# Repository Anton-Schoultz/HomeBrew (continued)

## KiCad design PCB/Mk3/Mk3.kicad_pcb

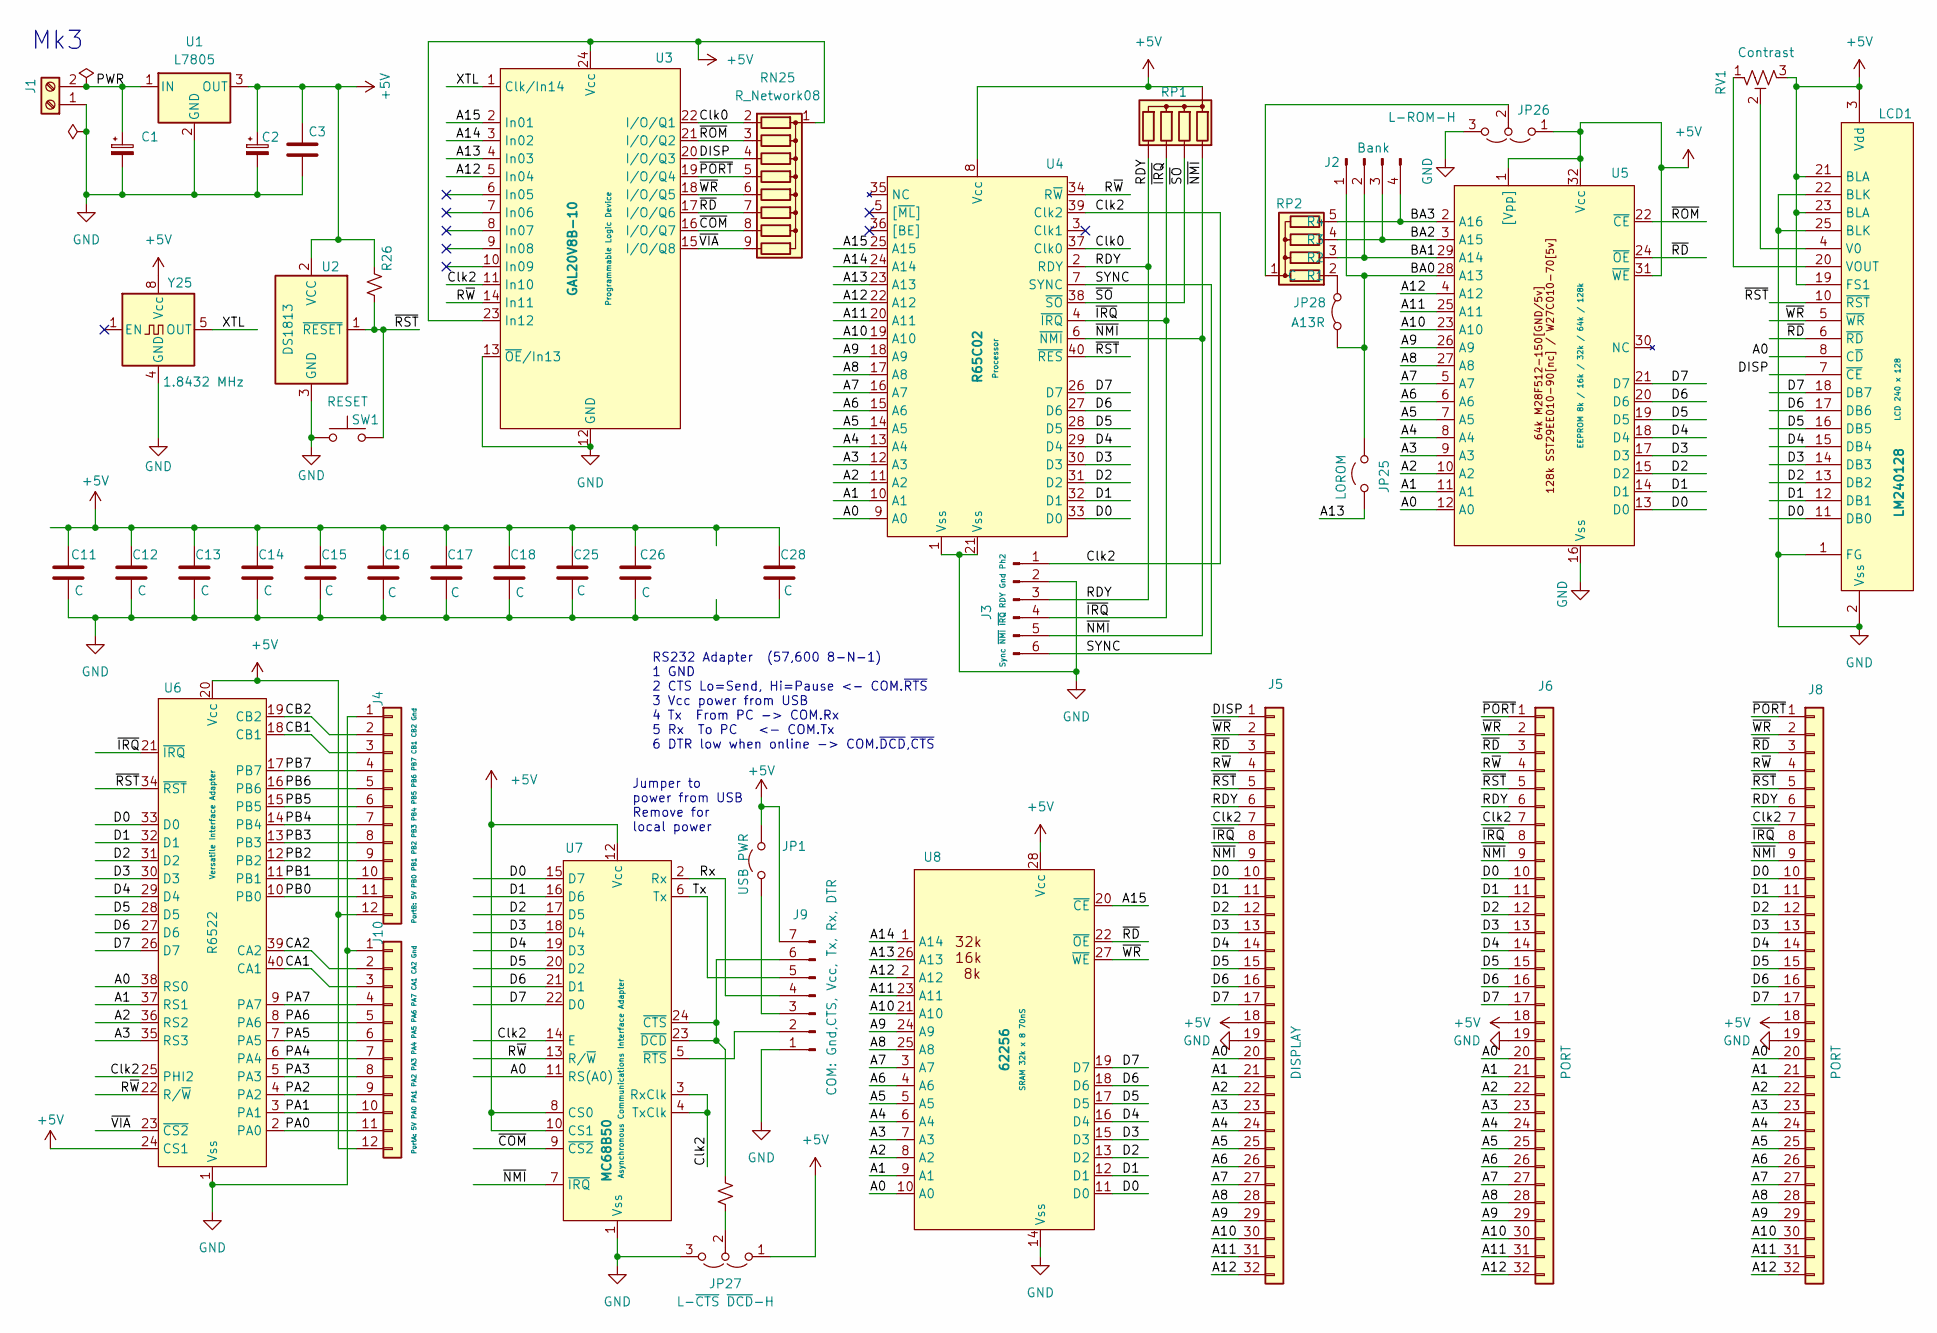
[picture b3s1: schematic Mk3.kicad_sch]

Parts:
C1, C2: C_Polarized_Small; CP_Radial_D10.0mm_P7.50mm
C3, C11, C12, C13, C14, C15, C16, C17, C18, C25, C26, C28: C; C_Disc_D7.5mm_W2.5mm_P5.00mm
J1: Power; TerminalBlock_MaiXu_MX126-5.0-02P_1x02_P5.00mm
J2: Bank; PinHeader_1x04_P2.54mm_Vertical
J3: Sync ~{NMI} ~{IRQ} RDY Gnd Ph2; PinHeader_1x06_P2.54mm_Vertical
J4: PortB: 5V PB0 PB1 PB2 PB3 PB4 PB5 PB6 PB7 CB1 CB2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; PinSocket_1x12_P2.54mm_Vertical
J5: DISPLAY; PinSocket_1x32_P2.54mm_Vertical
J6, J8: PORT; PinSocket_1x32_P2.54mm_Vertical
J9: COM: Gnd,CTS, Vcc, Tx, Rx, DTR; PinSocket_1x07_P2.54mm_Horizontal
J10: PortA: 5V PA0 PA1 PA2 PA3 PA4 PA5 PA6 PA7 CA1 CA2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; PinSocket_1x12_P2.54mm_Vertical
JP1: USB PWR; PinHeader_1x02_P2.54mm_Vertical
JP25: LOROM; PinHeader_1x02_P2.54mm_Vertical
JP26: L-ROM-H; PinHeader_1x03_P2.54mm_Vertical
JP27: L-~{CTS} ~{DCD}-H; PinHeader_1x03_P2.54mm_Vertical
JP28: A13R; SolderJumper-2_P1.3mm_Bridged_RoundedPad1.0x1.5mm
LCD1: LM240128; LCD 240x128
R25: PUp; R_Axial_DIN0204_L3.6mm_D1.6mm_P7.62mm_Horizontal
R26: R_Small_US; R_Axial_DIN0204_L3.6mm_D1.6mm_P7.62mm_Horizontal
RN25: R_Network08; R_Array_SIP9
RP1, RP2: R_Array_SIP5
RV1: Contrast; Potentiometer_Piher_PT-15-V15_Vertical
SW1: RESET; SW_PUSH_1P1T_6x3.5mm_H4.3_APEM_MJTP1243
U1: L7805; TO-220-3_Vertical
U2: DS1813; TO-92L_Wide
U3: GAL20V8B-10; DIP-24_W7.62mm_LongPads
U4: R65C02; DIP-40_W15.24mm_LongPads
U5: EEPROM; DIP-32_W15.24mm_LongPads
U6: R6522; DIP-40_W15.24mm_LongPads
U7: MC68B50; DIP-24_W15.24mm_LongPads
U8: 62256; DIP-28_W15.24mm_LongPads
Y25: 1.8432 MHz; Oscillator_DIP-8

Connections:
+5V: C2.1, C3.1, C11.1, C12.1, C13.1, C14.1, C15.1, C16.1, C17.1, C18.1, C25.1, C26.1, C28.1, J4.12, J5.18, J6.18, J8.18, J9.7, J10.12, JP1.2 (B), JP26.1 (A), JP27.1 (A), LCD1.3 (Vdd), LCD1.19 (FS1), LCD1.21 (BLA), LCD1.23 (BLA), R26.1, RN25.1 (common), RP1.1 (C), RV1.3, U1.3 (OUT), U2.2 (VCC), U3.23 (In12), U3.24 (Vcc), U4.8 (Vcc), U5.1 ([Vpp]), U5.31 (~WE), U5.32 (Vcc), U6.20 (Vcc), U6.24 (CS1), U7.8 (CS0), U7.10 (CS1), U7.12 (Vcc), U8.28 (Vcc), Y25.8 (Vcc)
/A0: J5.20, J6.20, J8.20, LCD1.8 (C~D), U4.9 (A0), U5.12 (A0), U6.38 (RS0), U7.11 (RS(A0)), U8.10 (A0)
/A1: J5.21, J6.21, J8.21, U4.10 (A1), U5.11 (A1), U6.37 (RS1), U8.9 (A1)
/A2: J5.22, J6.22, J8.22, U4.11 (A2), U5.10 (A2), U6.36 (RS2), U8.8 (A2)
/A3: J5.23, J6.23, J8.23, U4.12 (A3), U5.9 (A3), U6.35 (RS3), U8.7 (A3)
/A4: J5.24, J6.24, J8.24, U4.13 (A4), U5.8 (A4), U8.6 (A4)
/A5: J5.25, J6.25, J8.25, U4.14 (A5), U5.7 (A5), U8.5 (A5)
/A6: J5.26, J6.26, J8.26, U4.15 (A6), U5.6 (A6), U8.4 (A6)
/A7: J5.27, J6.27, J8.27, U4.16 (A7), U5.5 (A7), U8.3 (A7)
/A8: J5.28, J6.28, J8.28, U4.17 (A8), U5.27 (A8), U8.25 (A8)
/A9: J5.29, J6.29, J8.29, U4.18 (A9), U5.26 (A9), U8.24 (A9)
/A10: J5.30, J6.30, J8.30, U4.19 (A10), U5.23 (A10), U8.21 (A10)
/A11: J5.31, J6.31, J8.31, U4.20 (A11), U5.25 (A11), U8.23 (A11)
/A12: J5.32, J6.32, J8.32, U3.5 (In04), U4.22 (A12), U5.4 (A12), U8.2 (A12)
/A13: JP25.1 (A), U3.4 (In03), U4.23 (A13), U8.26 (A13)
/A14: U3.3 (In02), U4.24 (A14), U8.1 (A14)
/A15: U3.2 (In01), U4.25 (A15), U8.20 (~CE)
/BA0: J2.1, JP25.2 (B), JP28.1 (A), U5.28 (A13)
/BA1: J2.2, RP2.3 (R2), U5.29 (A14)
/BA2: J2.3, RP2.4 (R3), U5.3 (A15)
/BA3: J2.4, RP2.5 (R4), U5.2 (A16)
/CA1: J10.3, U6.40 (CA1)
/CA2: J10.2, U6.39 (CA2)
/CB1: J4.3, U6.18 (CB1)
/CB2: J4.2, U6.19 (CB2)
/Clk0: RN25.2 (R1), U3.22 (I/O/Q1), U4.37 (Clk0)
/Clk2: J3.1, J5.7, J6.7, J8.7, U3.11 (In10), U4.39 (Clk2), U6.25 (PHI2), U7.3 (RxClk), U7.4 (TxClk), U7.14 (E)
/D0: J5.10, J6.10, J8.10, LCD1.11 (DB0), U4.33 (D0), U5.13 (D0), U6.33 (D0), U7.15 (D7), U8.11 (D0)
/D1: J5.11, J6.11, J8.11, LCD1.12 (DB1), U4.32 (D1), U5.14 (D1), U6.32 (D1), U7.16 (D6), U8.12 (D1)
/D2: J5.12, J6.12, J8.12, LCD1.13 (DB2), U4.31 (D2), U5.15 (D2), U6.31 (D2), U7.17 (D5), U8.13 (D2)
/D3: J5.13, J6.13, J8.13, LCD1.14 (DB3), U4.30 (D3), U5.17 (D3), U6.30 (D3), U7.18 (D4), U8.15 (D3)
/D4: J5.14, J6.14, J8.14, LCD1.15 (DB4), U4.29 (D4), U5.18 (D4), U6.29 (D4), U7.19 (D3), U8.16 (D4)
/D5: J5.15, J6.15, J8.15, LCD1.16 (DB5), U4.28 (D5), U5.19 (D5), U6.28 (D5), U7.20 (D2), U8.17 (D5)
/D6: J5.16, J6.16, J8.16, LCD1.17 (DB6), U4.27 (D6), U5.20 (D6), U6.27 (D6), U7.21 (D1), U8.18 (D6)
/D7: J5.17, J6.17, J8.17, LCD1.18 (DB7), U4.26 (D7), U5.21 (D7), U6.26 (D7), U7.22 (D0), U8.19 (D7)
/DISP: J5.1, LCD1.7 (~CE), RN25.4 (R3), U3.20 (I/O/Q3)
/PA0: J10.11, U6.2 (PA0)
/PA1: J10.10, U6.3 (PA1)
/PA2: J10.9, U6.4 (PA2)
/PA3: J10.8, U6.5 (PA3)
/PA4: J10.7, U6.6 (PA4)
/PA5: J10.6, U6.7 (PA5)
/PA6: J10.5, U6.8 (PA6)
/PA7: J10.4, U6.9 (PA7)
/PB0: J4.11, U6.10 (PB0)
/PB1: J4.10, U6.11 (PB1)
/PB2: J4.9, U6.12 (PB2)
/PB3: J4.8, U6.13 (PB3)
/PB4: J4.7, U6.14 (PB4)
/PB5: J4.6, U6.15 (PB5)
/PB6: J4.5, U6.16 (PB6)
/PB7: J4.4, U6.17 (PB7)
/PWR: C1.1, J1.2, U1.1 (IN)
/RDY: J3.3, J5.6, J6.6, J8.6, RP1.5 (R4), U4.2 (RDY)
/Rx: J9.4, U7.2 (Rx)
/R~W: J5.4, J6.4, J8.4, U3.14 (In11), U4.34 (R~W), U6.22 (R/~W), U7.13 (R/~W)
/SYNC: J3.6, U4.7 (SYNC)
/Tx: J9.5, U7.6 (Tx)
/XTL: U3.1 (Clk/In14), Y25.5 (OUT)
/~COM: RN25.8 (R7), U3.16 (I/O/Q7), U7.9 (~CS2)
/~IRQ: J3.4, J5.8, J6.8, J8.8, RP1.4 (R3), U4.4 (~IRQ), U6.21 (~IRQ)
/~NMI: J3.5, J5.9, J6.9, J8.9, RP1.2 (R1), U4.6 (~NMI), U7.7 (~IRQ)
/~PORT: J6.1, J8.1, RN25.5 (R4), U3.19 (I/O/Q4)
/~RD: J5.3, J6.3, J8.3, LCD1.6 (~RD), RN25.7 (R6), U3.17 (I/O/Q6), U5.24 (~OE), U8.22 (~OE)
/~ROM: RN25.3 (R2), U3.21 (I/O/Q2), U5.22 (~CE)
/~RST: J5.5, J6.5, J8.5, LCD1.10 (~RST), R26.2, SW1.2, U2.1 (~RESET), U4.40 (~RES), U6.34 (~RST)
/~SO: RP1.3 (R2), U4.38 (~SO)
/~VIA: RN25.9 (R8), U3.15 (I/O/Q8), U6.23 (~CS2)
/~WR: J5.2, J6.2, J8.2, LCD1.5 (~WR), RN25.6 (R5), U3.18 (I/O/Q5), U8.27 (~WE)
GND: C1.2, C2.2, C3.2, C11.2, C12.2, C13.2, C14.2, C15.2, C16.2, C17.2, C18.2, C25.2, C26.2, C28.2, J1.1, J3.2, J4.1, J5.19, J6.19, J8.19, J9.1, J10.1, JP26.3 (B), JP27.3 (B), LCD1.1 (FG), LCD1.2 (Vss), LCD1.22 (BLK), LCD1.25 (BLK), SW1.1, U1.2 (GND), U2.3 (GND), U3.12 (GND), U3.13 (~OE/In13), U4.1 (Vss), U4.21 (Vss), U5.16 (Vss), U6.1 (Vss), U7.1 (Vss), U8.14 (Vss), Y25.4 (GND)
unnamed: J9.2, U7.5 (~RTS)
unnamed: J9.3, JP1.1 (A)
unnamed: J9.6, R25.2, U7.23 (~DCD), U7.24 (~CTS)
unnamed: JP26.2 (C), RP2.1 (C)
unnamed: JP27.2 (C), R25.1
unnamed: JP28.2 (B), RP2.2 (R1)
unnamed: LCD1.4 (V0), RV1.2
unnamed: LCD1.20 (VOUT), RV1.1

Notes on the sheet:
Mk3
RS232 Adapter (57,600 8-N-1) 1 GND 2 CTS Lo=Send, Hi=Pause <- COM.~{RTS} 3 Vcc power from USB 4 Tx From PC -> COM.Rx 5 Rx To PC <- COM.Tx 6 DTR low when online -> COM.~{DCD},~{CTS}
Jumper to power from USB Remove for local power

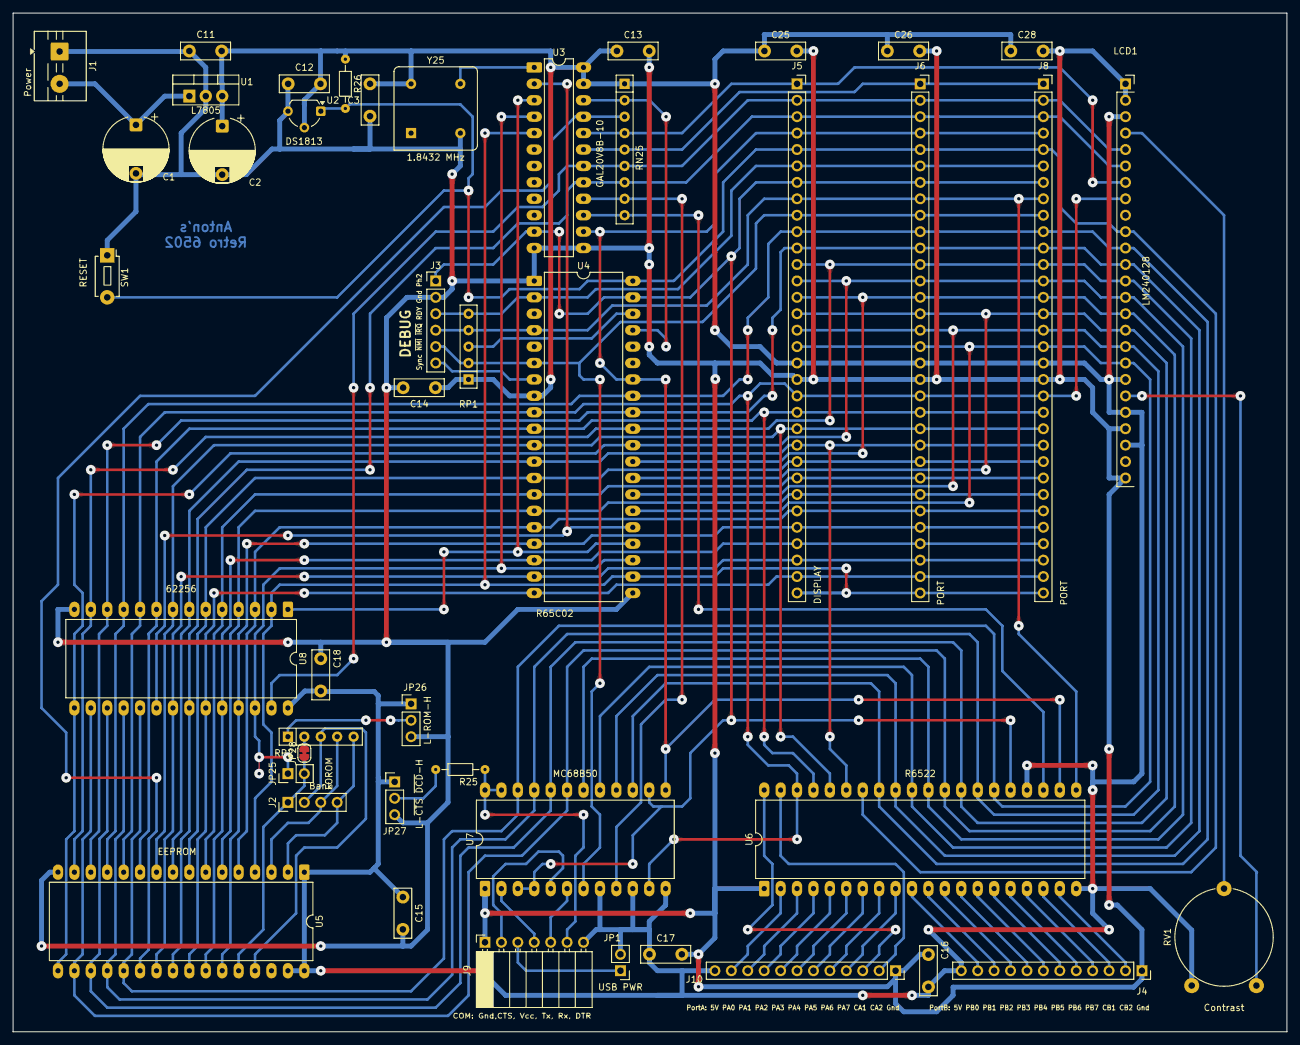
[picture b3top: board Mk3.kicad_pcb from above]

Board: 2 copper layers, 197.0 x 157.5 mm, 45 parts (0 on the bottom side), 78 nets.

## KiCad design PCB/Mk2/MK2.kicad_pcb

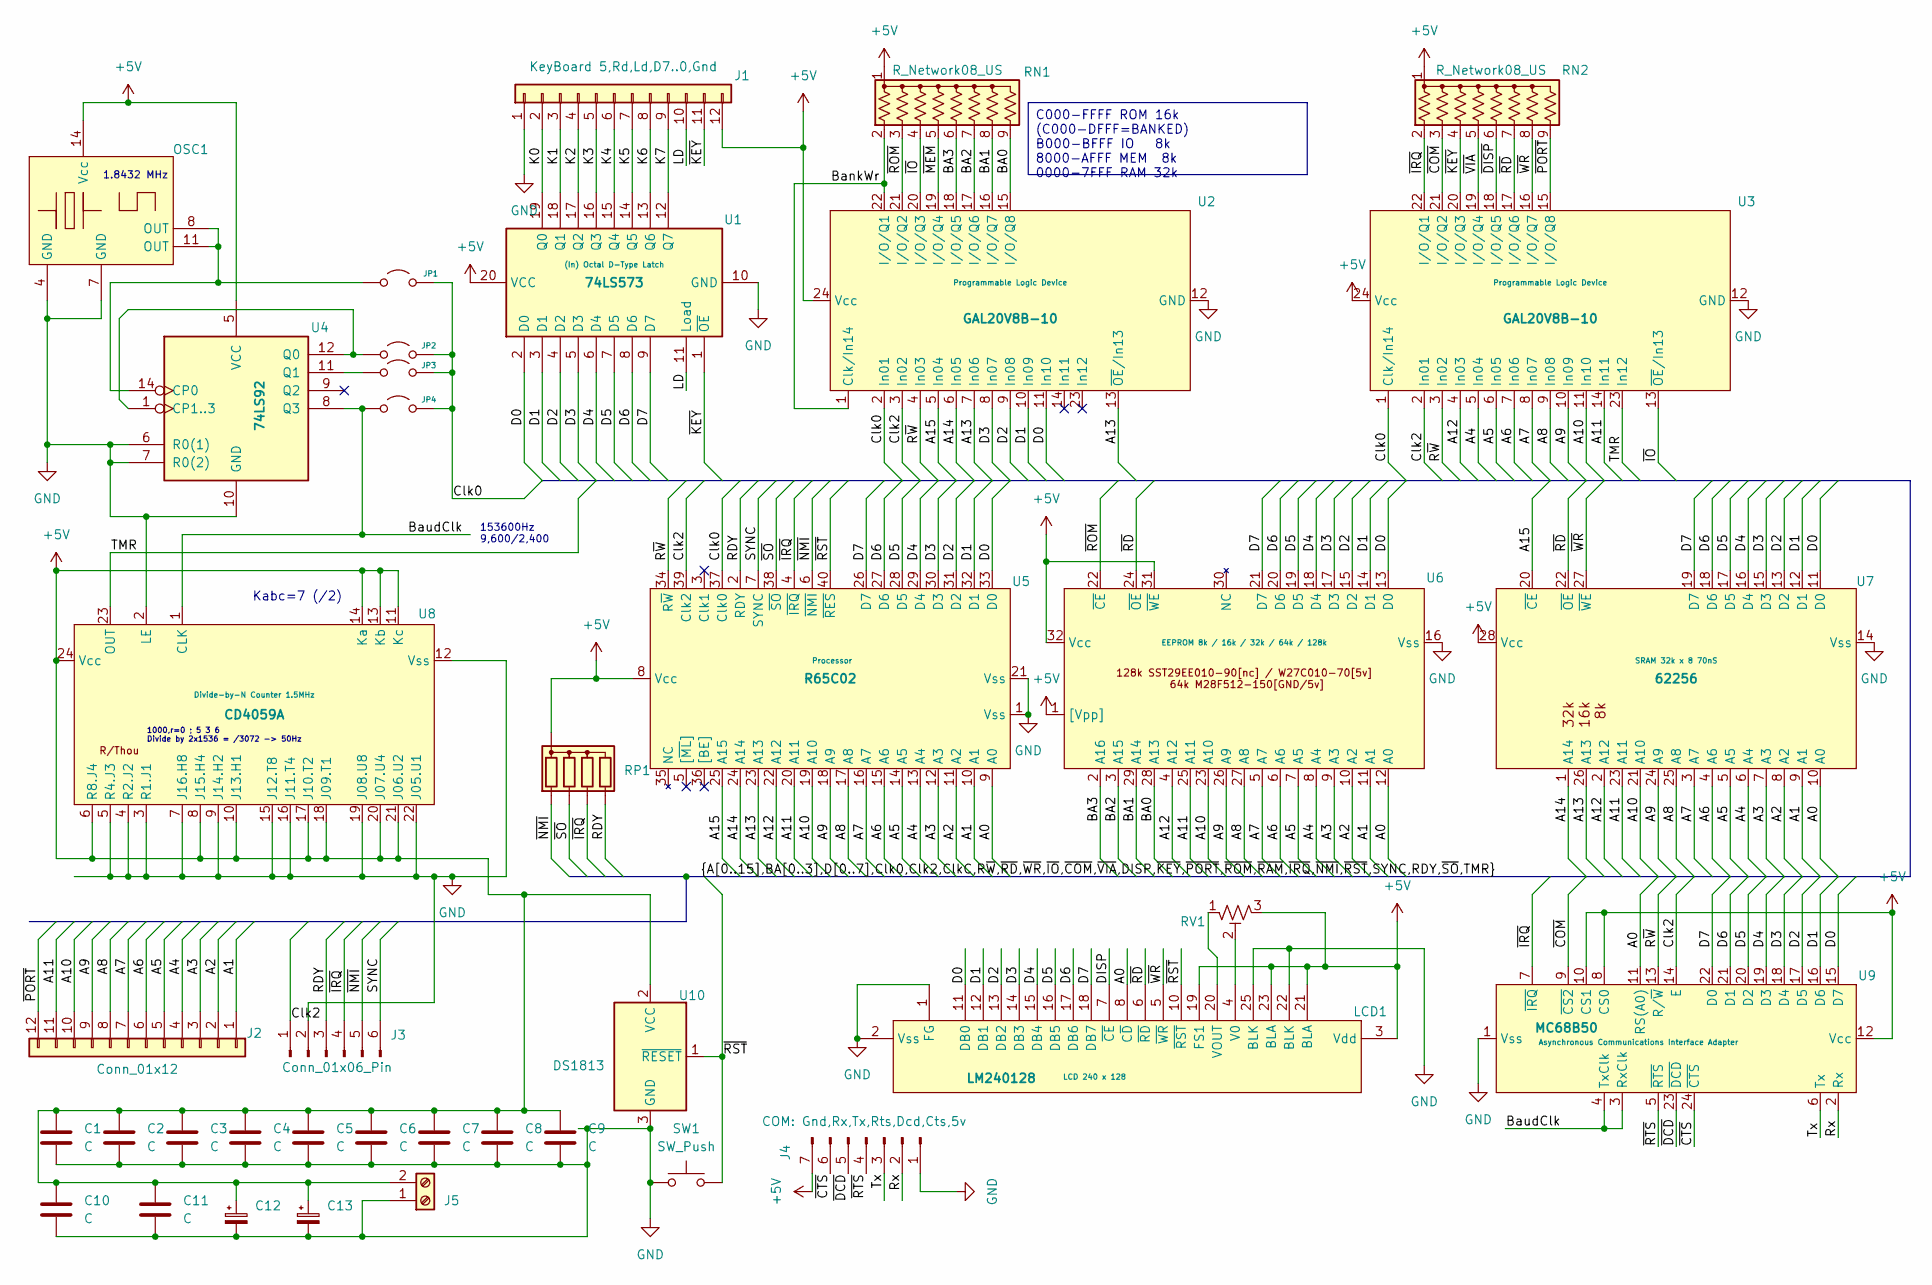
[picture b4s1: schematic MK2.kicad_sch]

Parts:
C1, C3, C4, C6, C7, C8, C9, C10: C; C_Disc_D7.5mm_W2.5mm_P5.00mm
C2, C5, C11: C; C_Rect_L11.0mm_W2.8mm_P10.00mm_MKT
C12, C13: C_Polarized_Small; CP_Radial_D10.0mm_P7.50mm
J1: KeyBoard 5,Rd,Ld,D7..0,Gnd; PinHeader_1x12_P2.54mm_Vertical
J2: Conn_01x12; PinSocket_1x12_P2.54mm_Vertical
J3: Conn_01x06_Pin; PinHeader_1x06_P2.54mm_Vertical
J4: COM: Gnd,Rx,Tx,Rts,Dcd,Cts,5v; PinSocket_1x07_P2.54mm_Horizontal
J5: Screw_Terminal_01x02; TerminalBlock_MaiXu_MX126-5.0-02P_1x02_P5.00mm
JP1, JP2, JP3, JP4: Jumper_2_Open; PinHeader_1x02_P2.54mm_Vertical
LCD1: LM240128; LCD 240x128
OSC1: DIP-14_W7.62mm_LongPads
RN1, RN2: R_Network08_US; R_Array_SIP9
RP1: R_Array_SIP5
RV1: R_Trim; Potentiometer_Runtron_RM-065_Vertical
SW1: SW_Push; MiniSwitch
U1: 74LS573; DIP-20_W7.62mm_LongPads
U2, U3: GAL20V8B-10; DIP-24_W7.62mm_LongPads
U4: 74LS92; DIP-14_W7.62mm
U5: R65C02; DIP-40_W15.24mm_LongPads
U6: EEPROM; DIP-32_W15.24mm_LongPads
U7: 62256; DIP-28_W15.24mm_LongPads
U8: CD4059A; DIP-24_W7.62mm_LongPads
U9: MC68B50; DIP-24_W15.24mm_LongPads
U10: DS1813; TO-92L_Inline

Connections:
+5V: C1.1, C2.1, C3.1, C4.1, C5.1, C6.1, C7.1, C8.1, C9.1, C10.1, C11.1, C12.1, C13.1, J1.12, J4.7, J5.2, LCD1.3 (Vdd), LCD1.19 (FS1), LCD1.21 (BLA), LCD1.23 (BLA), OSC1.14 (Vcc), RN1.1 (common), RN2.1 (common), RP1.1 (C), RV1.3, U1.20 (VCC), U2.24 (Vcc), U3.24 (Vcc), U4.5 (VCC), U5.8 (Vcc), U6.1 ([Vpp]), U6.31 (~WE), U6.32 (Vcc), U7.28 (Vcc), U8.6 (R8.J4), U8.8 (J15.H4), U8.10 (J13.H1), U8.11 (Kc), U8.13 (Kb), U8.14 (Ka), U8.17 (J10.T2), U8.18 (J09.T1), U8.20 (J07.U4), U8.21 (J06.U2), U8.24 (Vcc), U9.8 (CS0), U9.10 (CS1), U9.12 (Vcc), U10.2 (VCC)
/A0: LCD1.8 (C~D), U5.9 (A0), U6.12 (A0), U7.10 (A0), U9.11 (RS(A0))
/A1: J2.1, U5.10 (A1), U6.11 (A1), U7.9 (A1)
/A2: J2.2, U5.11 (A2), U6.10 (A2), U7.8 (A2)
/A3: J2.3, U5.12 (A3), U6.9 (A3), U7.7 (A3)
/A4: J2.4, U3.5 (In04), U5.13 (A4), U6.8 (A4), U7.6 (A4)
/A5: J2.5, U3.6 (In05), U5.14 (A5), U6.7 (A5), U7.5 (A5)
/A6: J2.6, U3.7 (In06), U5.15 (A6), U6.6 (A6), U7.4 (A6)
/A7: J2.7, U3.8 (In07), U5.16 (A7), U6.5 (A7), U7.3 (A7)
/A8: J2.8, U3.9 (In08), U5.17 (A8), U6.27 (A8), U7.25 (A8)
/A9: J2.9, U3.10 (In09), U5.18 (A9), U6.26 (A9), U7.24 (A9)
/A10: J2.10, U3.11 (In10), U5.19 (A10), U6.23 (A10), U7.21 (A10)
/A11: J2.11, U3.14 (In11), U5.20 (A11), U6.25 (A11), U7.23 (A11)
/A12: U3.4 (In03), U5.22 (A12), U6.4 (A12), U7.2 (A12)
/A13: U2.7 (In06), U2.13 (~OE/In13), U5.23 (A13), U7.26 (A13)
/A14: U2.6 (In05), U5.24 (A14), U7.1 (A14)
/A15: U2.5 (In04), U5.25 (A15), U7.20 (~CE)
/BA0: RN1.9 (R8), U2.15 (I/O/Q8), U6.28 (A13)
/BA1: RN1.8 (R7), U2.16 (I/O/Q7), U6.29 (A14)
/BA2: RN1.7 (R6), U2.17 (I/O/Q6), U6.3 (A15)
/BA3: RN1.6 (R5), U2.18 (I/O/Q5), U6.2 (A16)
/BankWr: RN1.2 (R1), U2.1 (Clk/In14), U2.22 (I/O/Q1)
/BaudClk: JP4.1 (A), U4.8 (Q3), U8.1 (CLK), U9.3 (RxClk), U9.4 (TxClk)
/Clk0: JP1.2 (B), JP2.2 (B), JP3.2 (B), JP4.2 (B), U2.2 (In01), U3.1 (Clk/In14), U5.37 (Clk0)
/Clk2: J3.1, U2.3 (In02), U3.2 (In01), U5.39 (Clk2), U9.14 (E)
/D0: LCD1.11 (DB0), U1.2 (D0), U2.11 (In10), U5.33 (D0), U6.13 (D0), U7.11 (D0), U9.15 (D7)
/D1: LCD1.12 (DB1), U1.3 (D1), U2.10 (In09), U5.32 (D1), U6.14 (D1), U7.12 (D1), U9.16 (D6)
/D2: LCD1.13 (DB2), U1.4 (D2), U2.9 (In08), U5.31 (D2), U6.15 (D2), U7.13 (D2), U9.17 (D5)
/D3: LCD1.14 (DB3), U1.5 (D3), U2.8 (In07), U5.30 (D3), U6.17 (D3), U7.15 (D3), U9.18 (D4)
/D4: LCD1.15 (DB4), U1.6 (D4), U5.29 (D4), U6.18 (D4), U7.16 (D4), U9.19 (D3)
/D5: LCD1.16 (DB5), U1.7 (D5), U5.28 (D5), U6.19 (D5), U7.17 (D5), U9.20 (D2)
/D6: LCD1.17 (DB6), U1.8 (D6), U5.27 (D6), U6.20 (D6), U7.18 (D6), U9.21 (D1)
/D7: LCD1.18 (DB7), U1.9 (D7), U5.26 (D7), U6.21 (D7), U7.19 (D7), U9.22 (D0)
/DISP: LCD1.7 (~CE)
/K0: J1.2, U1.19 (Q0)
/K1: J1.3, U1.18 (Q1)
/K2: J1.4, U1.17 (Q2)
/K3: J1.5, U1.16 (Q3)
/K4: J1.6, U1.15 (Q4)
/K5: J1.7, U1.14 (Q5)
/K6: J1.8, U1.13 (Q6)
/K7: J1.9, U1.12 (Q7)
/LD: J1.10, U1.11 (Load)
/RDY: J3.3, RP1.5 (R4), U5.2 (RDY)
/Rx: J4.2, U9.2 (Rx)
/R~W: U2.4 (In03), U3.3 (In02), U5.34 (R~W), U9.13 (R/~W)
/SYNC: J3.6, U5.7 (SYNC)
/TMR: U3.23 (In12), U8.23 (OUT)
/Tx: J4.3, U9.6 (Tx)
/~COM: RN2.3 (R2), U3.21 (I/O/Q2), U9.9 (~CS2)
/~CTS: J4.6, U9.24 (~CTS)
/~DCD: J4.5, U9.23 (~DCD)
/~DISP: RN2.6 (R5), U3.18 (I/O/Q5)
/~IO: RN1.4 (R3), U2.20 (I/O/Q3), U3.13 (~OE/In13)
/~IRQ: J3.4, RN2.2 (R1), RP1.4 (R3), U3.22 (I/O/Q1), U5.4 (~IRQ), U9.7 (~IRQ)
/~KEY: J1.11, RN2.4 (R3), U1.1 (~OE), U3.20 (I/O/Q3)
/~MEM: RN1.5 (R4), U2.19 (I/O/Q4)
/~NMI: J3.5, RP1.2 (R1), U5.6 (~NMI)
/~PORT: J2.12, RN2.9 (R8), U3.15 (I/O/Q8)
/~RD: LCD1.6 (~RD), RN2.7 (R6), U3.17 (I/O/Q6), U6.24 (~OE), U7.22 (~OE)
/~ROM: RN1.3 (R2), U2.21 (I/O/Q2), U6.22 (~CE)
/~RST: LCD1.10 (~RST), SW1.2, U5.40 (~RES), U10.1 (~RESET)
/~RTS: J4.4, U9.5 (~RTS)
/~SO: RP1.3 (R2), U5.38 (~SO)
/~VIA: RN2.5 (R4), U3.19 (I/O/Q4)
/~WR: LCD1.5 (~WR), RN2.8 (R7), U3.16 (I/O/Q7), U7.27 (~WE)
GND: C1.2, C2.2, C3.2, C4.2, C5.2, C6.2, C7.2, C8.2, C9.2, C10.2, C11.2, C12.2, C13.2, J1.1, J3.2, J4.1, J5.1, LCD1.1 (FG), LCD1.2 (Vss), LCD1.22 (BLK), LCD1.25 (BLK), OSC1.4 (GND), OSC1.7 (GND), SW1.1, U1.10 (GND), U2.12 (GND), U3.12 (GND), U4.6 (R0(1)), U4.7 (R0(2)), U4.10 (GND), U5.1 (Vss), U5.21 (Vss), U6.16 (Vss), U7.14 (Vss), U8.2 (LE), U8.3 (R1.J1), U8.4 (R2.J2), U8.5 (R4.J3), U8.7 (J16.H8), U8.9 (J14.H2), U8.12 (Vss), U8.15 (J12.T8), U8.16 (J11.T4), U8.19 (J08.U8), U8.22 (J05.U1), U9.1 (Vss), U10.3 (GND)
unnamed: JP1.1 (A), OSC1.8 (OUT), OSC1.11 (OUT), U4.14 (CP0)
unnamed: JP2.1 (A), U4.1 (CP1..3), U4.12 (Q0)
unnamed: JP3.1 (A), U4.11 (Q1)
unnamed: LCD1.4 (V0), RV1.2
unnamed: LCD1.20 (VOUT), RV1.1

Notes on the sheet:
Kabc=7 (/2)
1.8432 MHz
1000,r=0 ; 5 3 6 Divide by 2x1536 = /3072 -> 50Hz
153600Hz 9,600/2,400
C000-FFFF ROM 16k (C000-DFFF=BANKED) B000-BFFF IO 8k 8000-AFFF MEM 8k 0000-7FFF RAM 32k

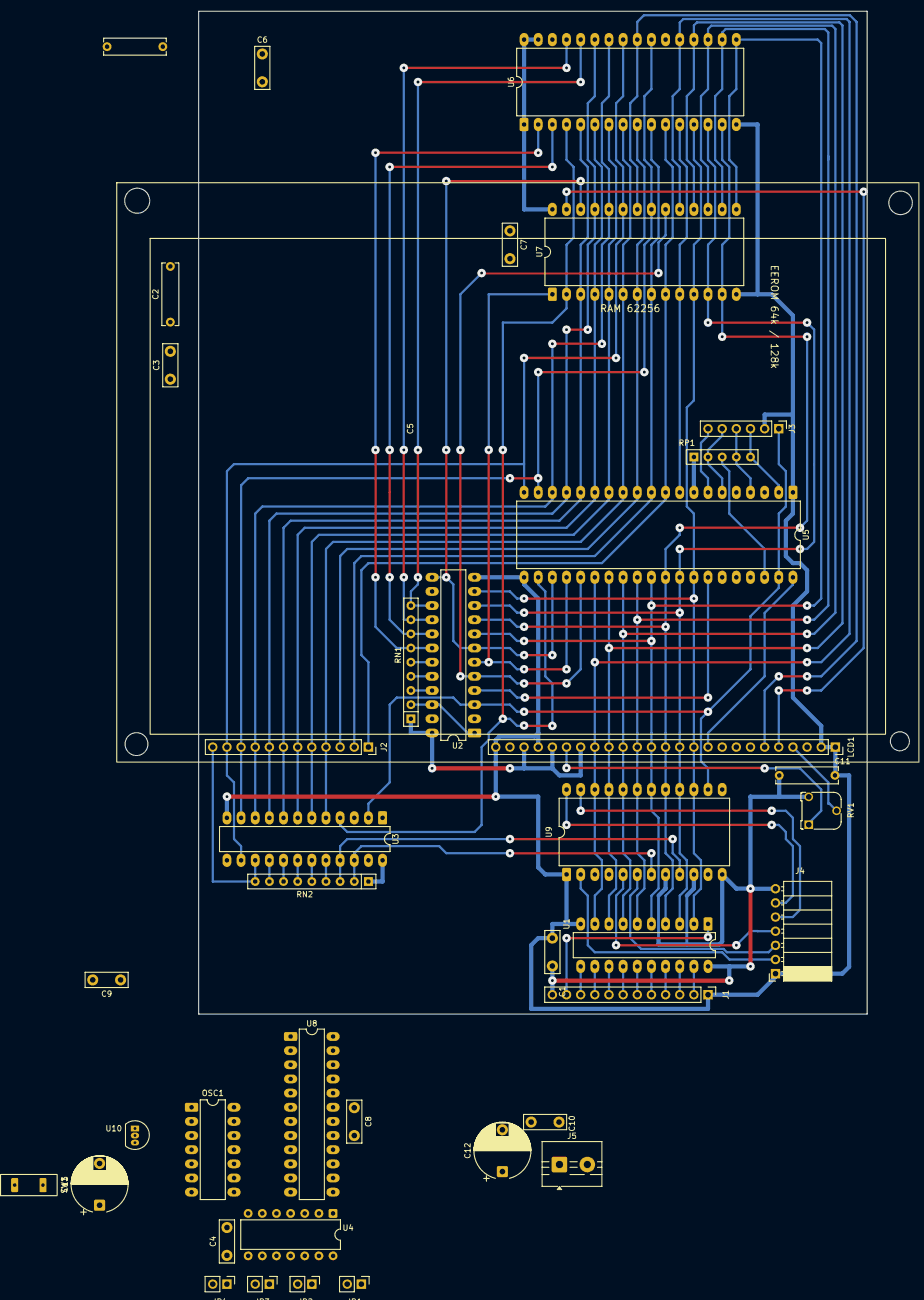
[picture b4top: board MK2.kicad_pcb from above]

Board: 2 copper layers, 141.4 x 180.0 mm, 39 parts (0 on the bottom side), 71 nets.

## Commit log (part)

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2024-11-11 GAL programmer (GAL20v8)
2024-11-11 Added Arduino section
2024-11-11 Added text
2024-11-11 Updated docs
2024-11-11 added pulseview links
2024-11-11 wincupl notes
2024-11-11 added pic of gal hat
2024-11-15 Added EEProgrammer code
2024-11-15 Added EE programmer and updated docs
2024-11-16 Updates to EEProgrammer to count zero bits. Added hex2bin tool
2024-11-19 Removed large install file for kicad-8.0.6-x86_64.exe
    Former-commit-id: 00c60aa45879fdb8a15821be57ce837079a9e464
2024-11-19 Updated read.me files
2024-12-12 Clock Circuit
2024-12-12 updated with pictures
2024-12-12 Fix diagram
2024-12-12 typo
2024-12-12 Datasheets added
2024-12-12 added history
2025-01-14 Renamed
2025-01-30 Additional Data sheets
2025-02-07 update IC labels
2025-02-07 Initial 6502 code bits
2025-02-07 Fix BufBlkWr
2025-02-07 Problem with buffer wrap around
2025-02-10 batch job for UltraEdit to assemble (using uz80as) and convert output
2025-02-12 Start Of Device work
2025-02-18 Modules and S16 Math
2025-02-18 CalcStr and CalcParse
2025-02-19 Save1
2025-02-19 More TestCode added
2025-02-21 Added CharRd, CharWr etc
2025-02-21 save
2025-02-22 Code pretty
2025-02-24 stack check, calc copies
2025-02-25 save point
2025-02-25 Parse & To String
2025-02-25 clean up
2025-02-25 Added rounding to the parse routine
2025-02-26 Adjust multiply result, apply sign and correct EXP for result -> NumA
2025-02-26 Div working, but integer result, need fractional part
2025-02-26 Divide working, problem with CalcStr, CalcStF etc
2025-02-26 Updated batch job, added AsmHelper.jar (asm formatter)
2025-03-03 Start of BASIC code
2025-03-03 Save point for BASIC
2025-03-03 TokFind fix
2025-03-03 Listing initial
2025-03-03 Print of decimal line no working
2025-03-03 NUMBER now 24 Bit
2025-03-03 24 bit macros for add,sub and shift
2025-03-03 24bit comments
2025-03-03 refactor
2025-03-04 Parse/List working?
2025-03-04 ReFormatted
2025-03-04 Updated Formatter (opcode to lowerCase)
2025-03-05 Fixes to Parsing routine
2025-03-06 Added IrqNmi.a65
2025-03-06 Parsing Tokens, Quoted-string, numeric, Var Names - the rest as-is.
2025-03-06 Added Zero blank / suppress
2025-03-06 Added list of Long VarName
2025-03-06 Changes to BREAK(n) handling, use with 'animate' Initial implementation of PRINT Indented echo info to make Assembler Messages stand out more
2025-03-06 Fix Print Number
2025-03-06 Change IntelHEX gen to map to $1000
2025-03-07 Added String and start of Eval
2025-03-07 DBuged StrClr, StrAdd, StrHead, StrTail, StrOut
2025-03-07 Added StrTrim
2025-03-07 Added & DBugged StrUpper, StrLower
2025-03-08 Execute of Print fixed :)
2025-03-08 Refactored Variable/Literal token parsing & listing
2025-03-09 Fixed list of var
2025-03-09 Fixes for long names, using bit7 to mark last char of name (or first if only one)
2025-03-10 Added tokenising of <= <> >=
2025-03-10 Refactoring
2025-03-12 Variables - Parse/list
2025-03-12 Keywords for tokenising
2025-03-12 Simple implementation of PRINT
2025-03-16 Add/Subtract OK, started Mul/Div
2025-03-16 Multiply seems OK, added brackets
2025-03-17 Refactor normalising
2025-03-17 Refactor float offset defs
2025-03-17 Div adjustment working
2025-03-17 Snap shot
2025-03-17 46783cy 385free
2025-03-17 357-44732
2025-03-17 tweak NumMul normalise
2025-03-17 tweak
2025-03-17 pre-tweak Div
2025-03-17 changed to 8k ROM
2025-03-18 pre change to sgn & exp as part of the 8 bytes
2025-03-18 using 8 byte unpacked form in Math - busy
2025-03-18 Added Util for general utilities (pointer access etc)
2025-03-18 Access methods Load/Save Float/Int
2025-03-18 fix zero suppression for -ve numbers
2025-03-18 fix blanking for -ve
2025-03-18 Reformat
2025-03-18 For divide - don't shift if low part is zero
2025-03-19 Pulled Maths out to separate 'module' with own ZPg declarations etc
2025-03-24 S16 add, sub, parse, print, pushA, popB OK
2025-03-24 NumMul, NumDiv, NumMod ok
2025-03-24 Main loop for testing
2025-03-24 added relational operators, problem in tokenizing '>' and '<' other are ok
2025-03-25 Relation operators working
2025-03-25 Fix print of zero, evaluate of braces
2025-03-25 Boolean operation AND,OR,XOR
2025-03-26 Implement LET for single char int vars - including math recalling values
2025-03-26 Refactored build control to use $ instead of redefining a variable
2025-03-26 Clean up, include the math module !
2025-03-26 Started work on Editor, added NEW
2025-03-27 Added Error handling, refactored display of message (Error and LIST share the same message print routine) Added char/hex substitution in the messages
2025-03-27 Moved constants from Vars to Constants file
2025-03-27 Fix EdtSeek, actions DEL/INS/ADD decoded, DEL/INS ready for implementation
2025-03-27 Document/clean
2025-03-27 Coded Editor INS,DEL,ADD seem OK. Added LIST
2025-04-08 Fix collection of args for LIST
2025-04-09 changes to line structure, work on editor and listing
2025-04-09 Fixes for List / tokenise line, start of XRun
2025-04-09 PRINT not working
2025-04-10 Print fixed
2025-04-10 debugging RUN
2025-04-10 Fixed list of REM keyword
2025-04-10 fixes to print ;
2025-04-10 Add NumLit as option for RUN, clean up main
2025-04-10 Notes on how GOTO/GOSUB will work
2025-04-11 Added IF <Expr> THEN <Statement>
2025-04-11 Fix bug in IntParse for '0' (high byte wrong)
2025-04-11 Change formatting for RUN
2025-04-11 clean up Main as warm start
2025-04-11 Faster NumCvt 2726 -> 1514 cycles (-1212 56%)
2025-04-11 Added GOSUB/RETURN
2025-04-11 Some refactoring
2025-04-11 Pre FOR/NEXT
2025-04-11 Part of FOR/NEXT done
2025-04-12 SAVE POINT - PRE CHANGE TO VAR ACCESS
2025-04-13 Initial FOR/NEXt - to be debugged
2025-04-14 FOR?NEXT OK, but tokenisation of math expression broken 'I*J' => 'IJ'
2025-04-14 BUG in Listing of expressions 'I*J' shows as 'IJ', code is tokenised correctly, runs OK
2025-04-14 Fix print of 0
2025-04-14 Added STEP size to FOR/NEXT and debugged
2025-04-14 Star Implementation of functions
2025-04-14 Implemented Function frame work, SQR(x) and RND(x) RND(x) code has a bug, gets stuck at 313 .. See NumRnd
2025-04-14 Clean Up unused code around function dev
2025-04-15 New Rand function - also added MOD of the arg RNDE(n) -> 0..(n-1)
2025-04-15 Cleanup
2025-04-15 Refactored Stack ops from math into common area Math.a65 - will reuse for string stack
2025-04-15 Initial String changes
2025-04-15 StrUpper, StrLower, StrPush, StrAdd seem OK
2025-04-15 Ready to add code to dimension, store and recall String variables
2025-04-15 Added CLEAR to clear all vars
2025-04-15 Initial code for StrGet, StrSet - to be tested
2025-04-15 Old RND() back, but commented out - bas distribution
2025-04-16 Added CLEAR and DIM Individual flags for debug sections, debug routines renamed DB_*
2025-04-16 Mods to listing control
2025-04-17 Debug String evaluator, start on string functions
2025-04-17 Debugged string functions, added LOWER$(~) Enhanced error messages to include caller's address
2025-04-17 Bug in PRINT
2025-04-17 Sort of working :^D
2025-04-17 Ready to implement LEFT$(<strexpr>,m)
2025-04-21 Implemented LEFT$(<StrExpr>,<NumExpr>)
2025-04-21 Implemented RIGHT$(<StrExpr>,<NumExpr>)
2025-04-21 Implemented MID$($,From,Len)
2025-04-21 Implemented MID$($,From,Length) and refactored common code into StrFunct
2025-04-21 Refactor to EvInt
2025-04-21 Implement subscripted string on LHS
2025-04-21 Refactor some of string variable access into StrFind
2025-04-21 Format
2025-04-22 Moved listing of offending line first
2025-04-22 ReArrange startup code, change NEW to Reset rather than just reset editor
2025-04-22 Added memory wipe code to Reset & EdtNew
2025-04-22 Fix detection of zero in NumDiv (was using Sgn,Exp instead of Lo,Hi)
2025-04-22 Fix editor issue, add quote mode for input UPPERCASE
2025-04-22 Todo updated
2025-04-23 Notes in Main
2025-04-23 Rework IntParse to use code in Math module instead of own code
2025-04-23 optimise some jsr xxx,rts to jmp xxx
2025-04-23 Changed to parse from pointer as prep for INPUT to read numeric value
2025-04-23 Clean up code and comments
2025-04-23 Document outstanding Keywords/ function for consideration
2025-04-23 Rename
2025-04-23 Readme file
2025-04-23 Fixes to readme
2025-04-23 Implemented ASC($)
2025-04-23 Implemented STR$({NumExpr})
2025-04-23 formating
2025-04-23 Updated documentation
2025-04-24 Implemented LEN( $ )
2025-04-24 Implemented FRE(#)
2025-04-24 Implemented PEEK({NumExpr}) and DEEK({NumExpr})
2025-04-24 Implemented POKE addr,byte and DOKE addr,word
2025-04-24 Add POKE & DOKE to All.a65
2025-04-24 Fix readme
2025-04-24 fix escapes
2025-04-24 Documentation/Comments
2025-04-24 Removed .export directives
2025-04-24 Removed unused/bad math module
2025-05-01 Work on s24 and refactor conversion
2025-05-01 NumSpc, NumSup and NumFmt moved to Math.a65 and made generic with constants
2025-05-01 Changed S24 to use 3bytes not 4 (no waste)
2025-05-02 Added string comparison to the IF statement, fixed listing or rel-ops
2025-05-02 Change GOTO to allow calculated destination line no
2025-05-02 Modified GOSUB to use expression for target, refactored code common with GOTO
2025-05-02 Simplified calculation of ZPtr in StrPoint
2025-05-02 Removed unused EVFLG
2025-05-02 Comment re formatting of numeric values for output
2025-05-05 Change accessing of variables to a more general form (prep for ForNext stack changes etc) Combined FOR, NEXT into one file
2025-05-05 Combined GOTO,GOSUB, RETURN into one file (removed individual ones)
2025-05-05 Refactor GOTO,GOSUB,RETURN eliminate duplicate error call, fall through
2025-05-05 Added combined files
2025-05-05 Change reading of characters
2025-05-05 Change to make seperate Char in/out to/from memory/io more explicit
2025-05-05 Remove unused routines and table data in Util
2025-05-05 Made message include math module version
2025-05-05 Remove commented out code, remove unused IO flags, clean up
2025-05-05 Clean FOR/NEXT
2025-05-05 Implemented device number re-routing of I/O
2025-05-05 Implemented simulated serial port ComSim.a65, add #n to PRINT and INPUT
2025-05-05 Set #n by rtn rather than direct, prep for SAVE
2025-05-05 Fix macro change that broke list :(
2025-05-05 Added COM init to LOAD/SAVE, clean up
2025-05-06 Reformatted all, updated files included in the project
2025-05-06 Updated documentation of the BASIC supported
2025-05-06 Updated formatter
2025-05-06 Simplified error message substitution (and saved code bytes)
2025-05-06 Added selectors for COMs and Console, added MC68B50 coms implementation refactored _Main
2025-05-06 Added code for Stae machine engine
2025-05-06 Reenable IRQs in SmInit
2025-05-07 Added keyboard buffer and keyboard state machine
2025-05-07 Debugging State Machine and keyboard
2025-05-07 Fix loop in NumCvt, added MathH24
2025-05-07 Add INT(~), Fix bugs in parse of number, zero suppression, tokenising of numbers starting with point
2025-05-08 Sorted keywords and functions, added FLOAT indicator
2025-05-08 Fix parsing of decimal for float / error for integer Add 'E' in front of error code Add 'error.' to end of error message Refactor handling of REM Check for decimals in PRINT
2025-05-08 Modified building inclusion and reporting Added stub for ConLCD
2025-05-08 Renamed module files and added (forgotten) file for LCD console ConLCD.a65
2025-05-08 UEdit keyword and config
2025-05-09 Changed Macros for Branching (corrected) BR_LT, BR_GT, BR_LE and BR_GT
2025-05-09 Modified to allow format all
2025-05-15 removed unused macro and code
2025-08-22 Save data
2025-09-23 PCB-20250923-0955
2025-09-23 PC-20250923-1122
2025-09-26 Parts library and blank sheet
2025-10-01 RestorePoint
2025-11-26 Mk3-a
2025-11-26 3d model and moved trim pot
2025-11-26 updated silk & foot prints
2026-01-13 Added Mk4 (from retor) to add expansion bus as well
2026-01-13 Added descriptions of each board variant
2026-01-19 Latest variation
2026-01-22 all done, pre-clk div
2026-01-26 Cleaned
2026-01-26 Added PCB file
2026-01-30 Pre Remap
